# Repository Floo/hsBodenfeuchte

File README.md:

hsBodenfeuchte
==============

Bodenfeuchtesensor mit RFduino und BT4.0

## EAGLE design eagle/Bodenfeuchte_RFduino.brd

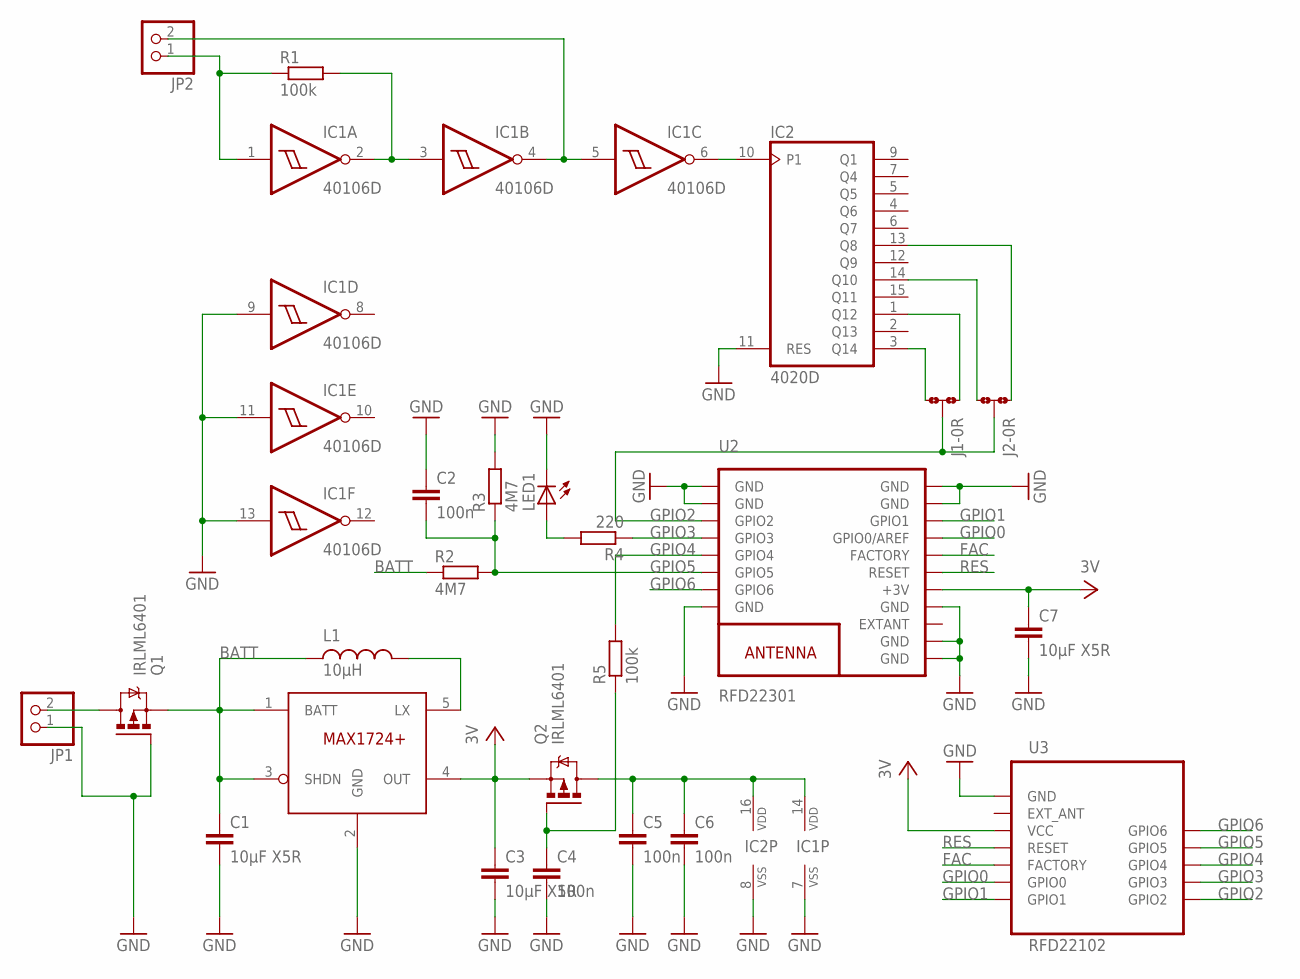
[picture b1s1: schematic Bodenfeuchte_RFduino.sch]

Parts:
C1, C3, C7: 10µF X5R; C0805
C2, C4, C5, C6: 100n; C0805
IC1: 40106D; SO14
IC2: 4020D; SO16
J1, J2: 0R-JUMPA; A0R-JMP
JP1, JP2: PINHD-1X2; 1X02
L1: 10µH; DS1608
LED1: LEDCHIPLED_1206; CHIPLED_1206
Q1, Q2: IRLML6401; MICRO3
R1, R5: 100k; R0805
R2, R3: 4M7; R0805
R4: 220; R0805
U1: MAX1724; SOT23-5L
U2: RFD22301
U3: RFD22102

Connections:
BATT: C1.1, L1.P$2, Q1.2 (S), R2.1, U1.1 (BATT), U1.3 (SHDN)
FAC: U2.15 (FACTORY), U3.FACTORY
GND: C1.2, C2.1, C3.2, C4.2, C5.2, C6.2, C7.2, IC1.7 (VSS), IC1.9 (I), IC1.11 (I), IC1.13 (I), IC2.8 (VSS), IC2.11 (RES), JP1.1, LED1.C, Q1.1 (G), R3.2, U1.2 (GND), U2.1 (GND), U2.2 (GND), U2.8 (GND), U2.9 (GND), U2.10 (GND), U2.12 (GND), U2.18 (GND), U2.19 (GND), U3.GND
GPIO0: U2.16 (GPIO0/AREF), U3.GPIO0
GPIO1: U2.17 (GPIO1), U3.GPIO1
GPIO2: J1.2, J2.2, U2.3 (GPIO2), U3.GPIO2
GPIO3: R4.1, U2.4 (GPIO3), U3.GPIO3
GPIO4: R5.2, U2.5 (GPIO4), U3.GPIO4
GPIO5: C2.2, R2.2, R3.1, U2.6 (GPIO5), U3.GPIO5
GPIO6: U2.7 (GPIO6), U3.GPIO6
unnamed: L1.P$1, U1.5 (LX)
unnamed: JP1.2, Q1.3 (D)
unnamed: LED1.A, R4.2
unnamed: IC2.1 (Q12), J1.1
unnamed: IC1.6 (O), IC2.10 (P1)
unnamed: IC1.4 (O), IC1.5 (I), JP2.2
unnamed: IC1.2 (O), IC1.3 (I), R1.2
unnamed: C4.1, Q2.1 (G), R5.1
unnamed: C5.1, C6.1, IC1.14 (VDD), IC2.16 (VDD), Q2.3 (D)
unnamed: IC1.1 (I), JP2.1, R1.1
unnamed: IC2.14 (Q10), J2.3
unnamed: IC2.13 (Q8), J2.1
unnamed: IC2.3 (Q14), J1.3
RES: U2.14 (RESET), U3.RESET
VCC: C3.1, C7.1, Q2.2 (S), U1.4 (OUT), U2.13 (+3V), U3.VCC

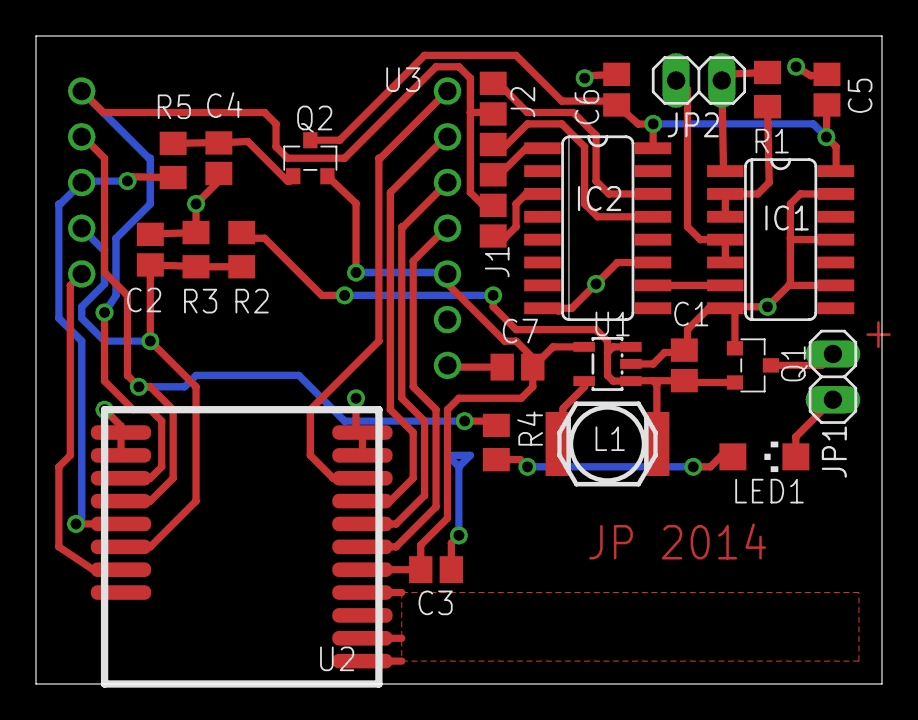
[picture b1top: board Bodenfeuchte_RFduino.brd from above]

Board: 2 copper layers, 47.0 x 36.0 mm, 25 parts (0 on the bottom side), 25 nets.

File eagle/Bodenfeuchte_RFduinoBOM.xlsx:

Anzahl | Part | Value | Device | Package | Lieferant | Best.-Nr. | Preis | Preis pro Einheit
3 | C1, C3, C7 | 10µF X5R | SMD Kondensator | 0805 | Reichelt | X5R-G0805 10/16 | 0.06 | 0.18
4 | C2, C4, C5, C6 | 100n | SMD Kondensator | 0805 | Reichelt | X7R-G0805 100N | 0.05 | 0.2
1 | IC1 | HCF40106B | IC | SO14 | Reichelt | SMD 40106 | 0.17 | 0.17
1 | IC2 | HCF4020B | IC | SO16 | Reichelt | SMD 4020 | 0.33 | 0.33
2 | J1, J2 | 0R | SMD-Widerstand | 0805 | Reichelt | SMD-0805 0,00 | 0.10199999999999999 | 0.20399999999999999
2 | JP1, JP2 |  | Pfostenleiste | 1X02 | Reichelt |  |  | 0
1 | L1 | 10µH | DS1608C |  | Coilcraft |  |  | 0
1 | LED1 |  | SMD-LED | 1206 | Reichelt | SMD-LED 1206 GN | 0.1 | 0.1
2 | Q1, Q2 | IRLML6401 | SMD-FET | MICRO3 | Reichelt |  | 0.15 | 0.3
2 | R1, R5 | 100k | SMD Widerstand | 0805 | Reichelt | SMD-0805 100K | 0.10299999999999999 | 0.20599999999999999
2 | R2, R3 | 4M7 | SMD Widerstand | 0805 | Reichelt | SMD-0805 4M7 | 0.10299999999999999 | 0.20599999999999999
1 | R4 | 220 R | SMD Widerstand | 0805 | Reichelt | SMD-0805 200 | 0.10299999999999999 | 0.10299999999999999
1 | U1 | MAX1724 | MAX1724 | SOT23-5L | Maxim |  |  | 0
1 | U2 | RFD22301 | RFD22301 | RFD22301 | RFduino |  |  | 0
1 | U3 | RFD22102 | RFD22102 | RFD22102 | RFduino |  |  | 0
 |  |  |  |  |  |  |  | 1.9990000000000001

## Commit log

2014-09-05 inital commit
2014-09-07 Inbetriebnahme
2014-09-08 pdf für eagle
2014-09-10 Struct für Sendevorgang eingefügt
